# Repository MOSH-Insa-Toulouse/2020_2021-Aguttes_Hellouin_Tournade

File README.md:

# 2020_2021-Aguttes_Hellouin_Tournade

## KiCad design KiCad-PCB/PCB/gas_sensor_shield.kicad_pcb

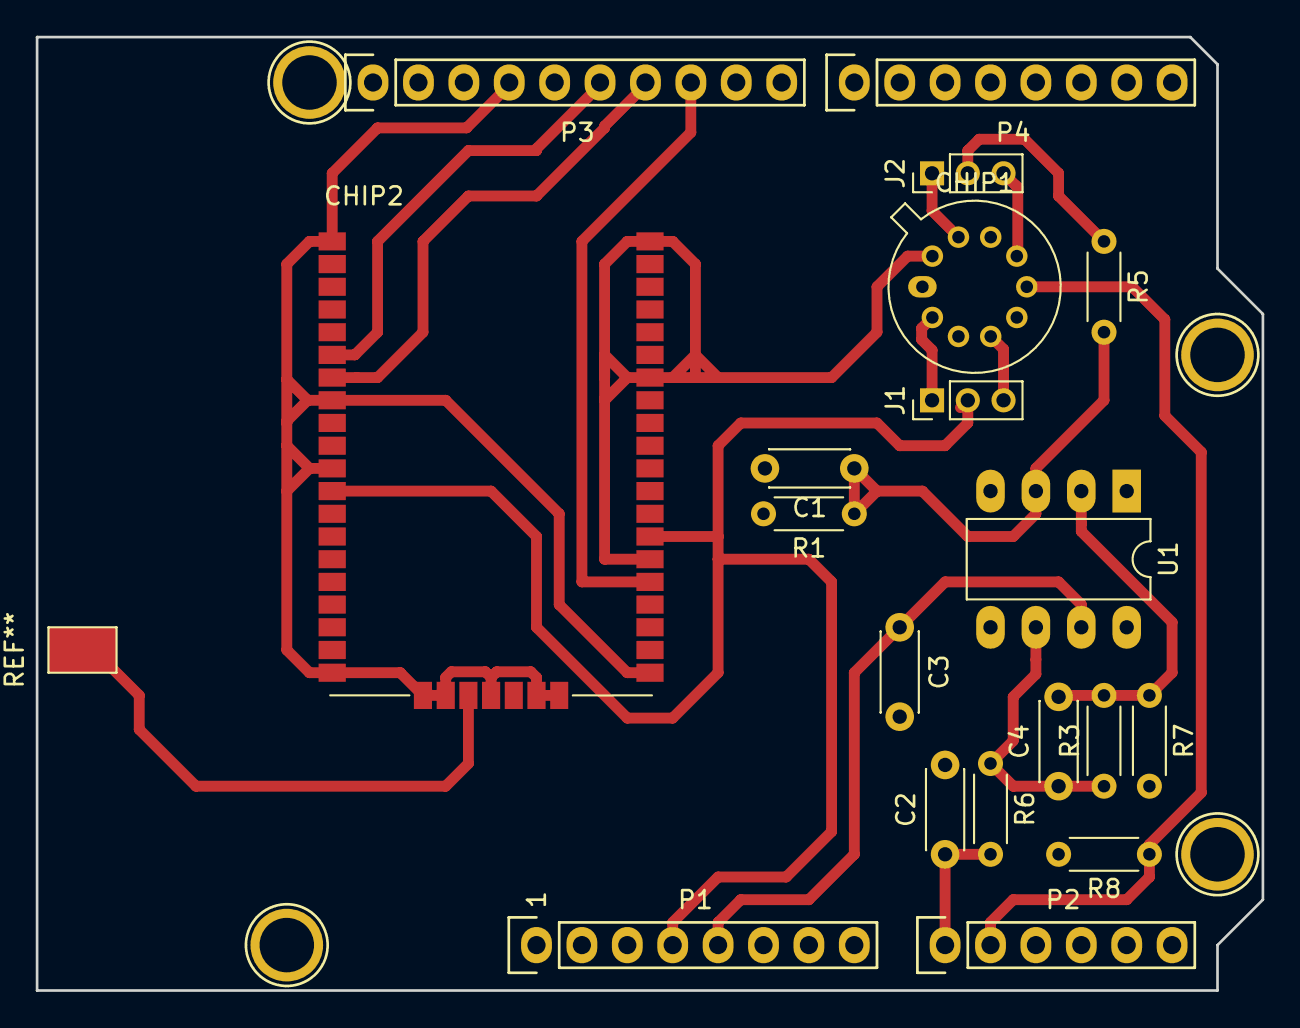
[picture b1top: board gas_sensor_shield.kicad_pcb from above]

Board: 2 copper layers, 68.6 x 53.3 mm, 23 parts (0 on the bottom side), 16 nets.

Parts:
C1, C2, C3: 100n; C_Disc_D4.3mm_W1.9mm_P5.00mm
C4: 1u; C_Disc_D4.3mm_W1.9mm_P5.00mm
CHIP1: Sensor_GAS_AIME; TO-5-10_Window
CHIP2: RN2483
J1, J2: Conn_01x03; PinHeader_1x03_P2.00mm_Vertical
P1: Power; Socket_Strip_Arduino_1x08
P2: Analog; Socket_Strip_Arduino_1x06
P3: Digital; Socket_Strip_Arduino_1x10
P4: Digital; Socket_Strip_Arduino_1x08
P5, P6, P7, P8: CONN_01X01; Arduino_1pin
R1, R3: 100k; R_Axial_DIN0204_L3.6mm_D1.6mm_P5.08mm_Horizontal
R5: 10k; R_Axial_DIN0204_L3.6mm_D1.6mm_P5.08mm_Horizontal
R6, R7: 1k; R_Axial_DIN0204_L3.6mm_D1.6mm_P5.08mm_Horizontal
R8: R; R_Axial_DIN0204_L3.6mm_D1.6mm_P5.08mm_Horizontal
U1: LTC1050; DIP-8_W7.62mm_LongPads

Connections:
+3V3: CHIP2.12, CHIP2.34, J1.2, P1.4
+5V: C3.1, P1.5, U1.7
GND: C1.2, C2.2, C3.2, CHIP1.5, CHIP1.10, CHIP2.1, CHIP2.8, CHIP2.11, CHIP2.20, CHIP2.21, CHIP2.22, CHIP2.24, CHIP2.26, CHIP2.27, CHIP2.28, CHIP2.33, CHIP2.41, CHIP2.47, P1.6, P1.7, P3.4, R1.2, R7.2, R8.2, U1.4
Gas_Sensor: J2.2, R5.1
Gas_Sensor_out: C2.1, P2.1, R6.2
LORA_RX: CHIP2.7, P3.7
LORA_TX: CHIP2.6, P3.6
unnamed: C1.1, R1.1, R5.2, U1.3
unnamed: C4.1, R3.1, R6.1, U1.6
unnamed: C4.2, R3.2, R7.1, U1.2
unnamed: CHIP1.2, J1.1
unnamed: CHIP1.4, J1.3
unnamed: CHIP1.7, J2.3
unnamed: CHIP1.9, J2.1
RESET: CHIP2.32, P3.8
Temp_Sensor: CHIP1.6, P2.2, R8.1
